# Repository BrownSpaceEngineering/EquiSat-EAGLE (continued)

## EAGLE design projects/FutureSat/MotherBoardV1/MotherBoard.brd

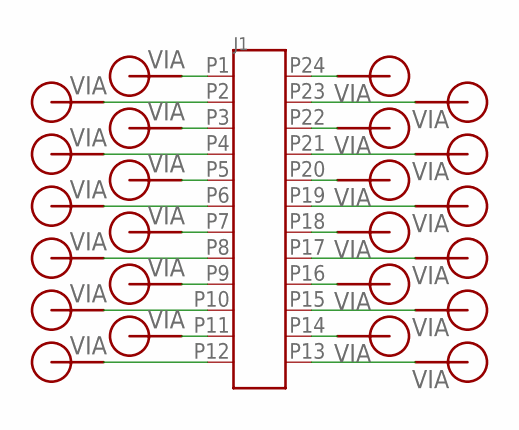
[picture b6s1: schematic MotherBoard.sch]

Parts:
J1: EBM12DRXH
V1, V2, V3, V4, V5, V6, V7, V8, V9, V10, V11, V12, V13, V14, V15, V16, V17, V18, V19, V20, V21, V22, V23, V24: VIA60MIL-SQ; VIA-60MIL-SQ

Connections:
unnamed: J1.P1, V1.P$1
unnamed: J1.P2, V2.P$1
unnamed: J1.P3, V3.P$1
unnamed: J1.P4, V4.P$1
unnamed: J1.P5, V5.P$1
unnamed: J1.P6, V6.P$1
unnamed: J1.P7, V7.P$1
unnamed: J1.P8, V8.P$1
unnamed: J1.P9, V9.P$1
unnamed: J1.P10, V10.P$1
unnamed: J1.P11, V11.P$1
unnamed: J1.P12, V12.P$1
unnamed: J1.P13, V13.P$1
unnamed: J1.P14, V14.P$1
unnamed: J1.P15, V15.P$1
unnamed: J1.P16, V16.P$1
unnamed: J1.P17, V17.P$1
unnamed: J1.P18, V18.P$1
unnamed: J1.P19, V19.P$1
unnamed: J1.P20, V20.P$1
unnamed: J1.P21, V21.P$1
unnamed: J1.P22, V22.P$1
unnamed: J1.P23, V23.P$1
unnamed: J1.P24, V24.P$1

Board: 2 copper layers, 25 parts (0 on the bottom side), 24 nets, no tracks yet.

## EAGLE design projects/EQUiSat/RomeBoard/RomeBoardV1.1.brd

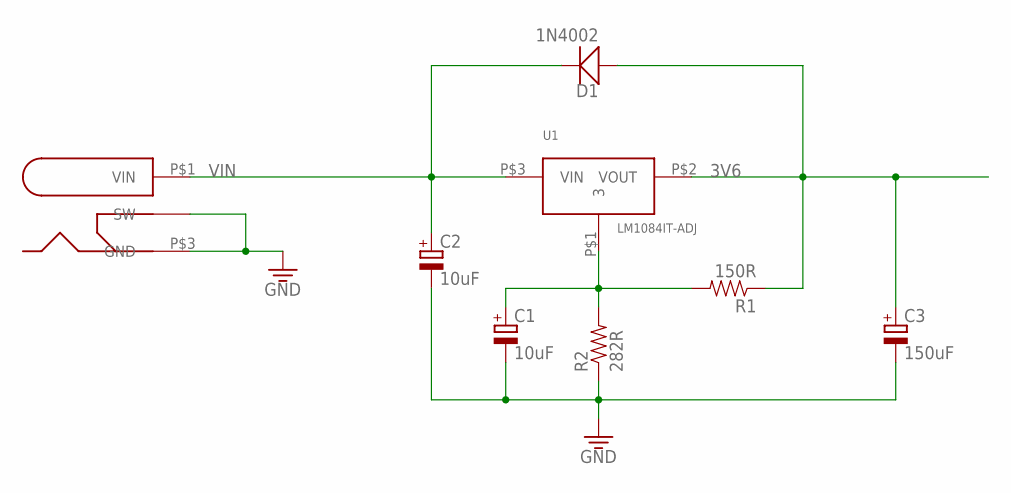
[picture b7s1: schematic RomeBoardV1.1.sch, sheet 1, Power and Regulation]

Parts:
C1, C2: 10uF; E2,5-7
C3: 150uF; E5-13
D1: 1N4002; DO-201AD
R1: 150R; AXIAL-0.4
R2: 282R; AXIAL-0.4
U1: LM1084IT-ADJ; TO-220-507302B00000G
U$2: PJ-002A

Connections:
3V6: C3.+, D1.P$1 (A), R1.1, U1.P$2 (VOUT); also elsewhere on the board
GND: C1.-, C2.-, C3.-, R2.1, U$2.P$2 (SW), U$2.P$3 (GND); also elsewhere on the board
unnamed: C1.+, R1.2, R2.2, U1.P$1 (3)
VIN: C2.+, D1.P$2 (C), U1.P$3 (VIN), U$2.P$1 (VIN); also elsewhere on the board

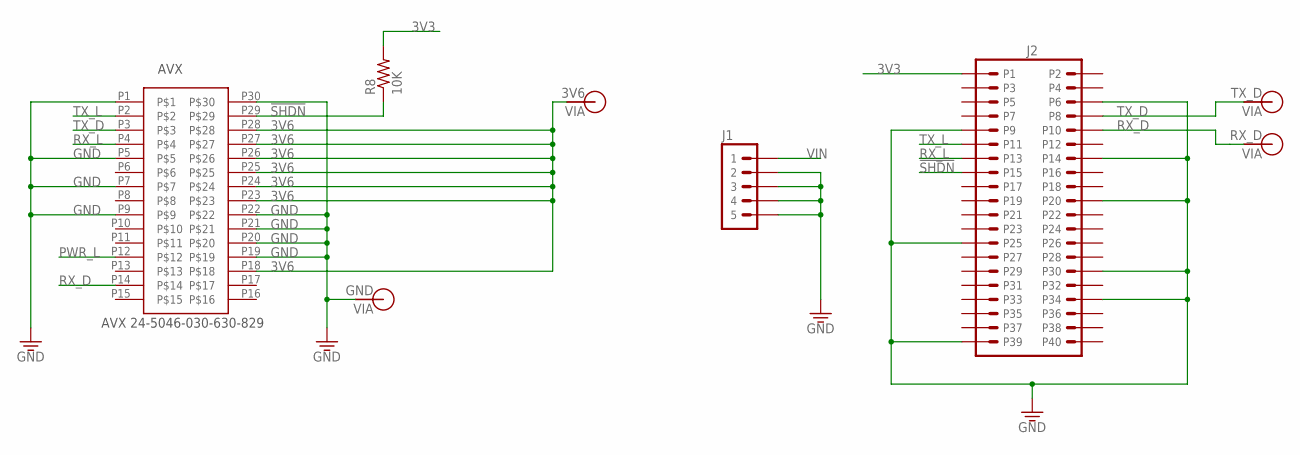
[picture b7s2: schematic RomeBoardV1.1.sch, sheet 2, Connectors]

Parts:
AVX: AVX-24-5046-030-630-829; AVX-24-5046-630-829
J1: HEADER-5; HEADER-05
J2: RASPBERRY-PI-HEADER; HEADER-20X02
R8: 10K; AXIAL-0.4
V1: TX_D; VIA-120MIL
V2: RX_D; VIA-120MIL
V4: GND; VIA-120MIL
V5: 3V6; VIA-120MIL

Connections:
3V3: J2.P1, R8.2
3V6: AVX.P18, AVX.P23, AVX.P24, AVX.P25, AVX.P26, AVX.P27, AVX.P28, V5.P$1; also elsewhere on the board
!SHDN: AVX.P29, J2.P15, R8.1
GND: AVX.P1, AVX.P5, AVX.P7, AVX.P9, AVX.P19, AVX.P20, AVX.P21, AVX.P22, AVX.P30, J1.2, J1.3, J1.4, J1.5, J2.P6, J2.P9, J2.P14, J2.P20, J2.P25, J2.P30, J2.P34, J2.P39, V4.P$1; also elsewhere on the board
PWR_L: AVX.P12; also elsewhere on the board
RX_D: AVX.P14, J2.P10, V2.P$1
RX_L: AVX.P4, J2.P13; also elsewhere on the board
TX_D: AVX.P3, J2.P8, V1.P$1
TX_L: AVX.P2, J2.P11; also elsewhere on the board
VIN: J1.1; also elsewhere on the board

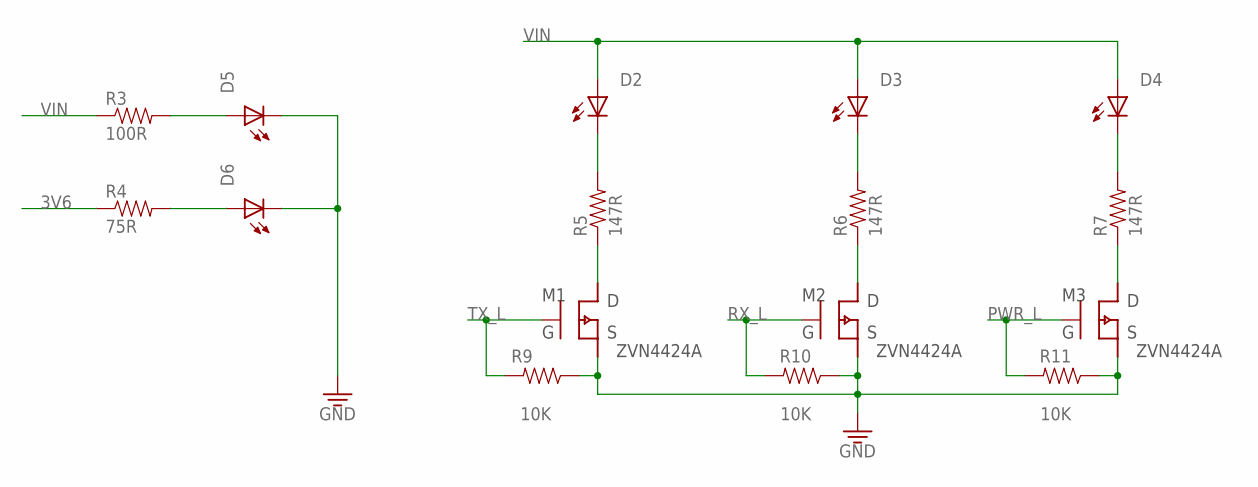
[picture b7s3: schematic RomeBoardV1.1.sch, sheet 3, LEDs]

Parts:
D2, D3, D4, D5, D6: LEDTHRU-HOLE-CONNECTOR; 1X2-POL
M1, M2, M3: ZVN4424A; TO-923-MOS
R3: 100R; AXIAL-0.4
R4: 75R; AXIAL-0.4
R5, R6, R7: 147R; AXIAL-0.4
R9, R10, R11: 10K; AXIAL-0.4

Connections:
3V6: R4.1; also elsewhere on the board
GND: D5.2 (C), D6.2 (C), M1.3 (S), M2.3 (S), M3.3 (S), R9.1, R10.1, R11.1; also elsewhere on the board
unnamed: D5.1 (A), R3.2
unnamed: D6.1 (A), R4.2
unnamed: D3.2 (C), R6.2
unnamed: M1.1 (D), R5.1
unnamed: M2.1 (D), R6.1
unnamed: M3.1 (D), R7.1
unnamed: D4.2 (C), R7.2
unnamed: D2.2 (C), R5.2
PWR_L: M3.2 (G), R11.2; also elsewhere on the board
RX_L: M2.2 (G), R10.2; also elsewhere on the board
TX_L: M1.2 (G), R9.2; also elsewhere on the board
VIN: D2.1 (A), D3.1 (A), D4.1 (A), R3.1; also elsewhere on the board

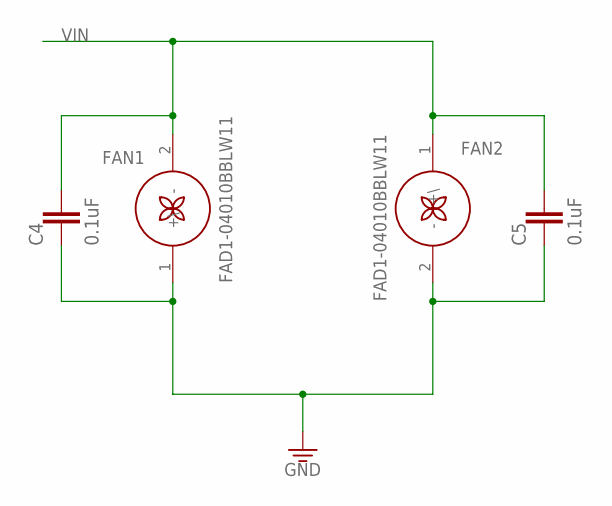
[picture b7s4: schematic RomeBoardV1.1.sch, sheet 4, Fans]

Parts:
C4, C5: 0.1uF; C050-025X075
FAN1, FAN2: FAD1-04010BBLW11; 1X2-POL

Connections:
GND: C4.2, C5.2, FAN1.1 (+\), FAN2.2 (-); also elsewhere on the board
VIN: C4.1, C5.1, FAN1.2 (-), FAN2.1 (+\); also elsewhere on the board

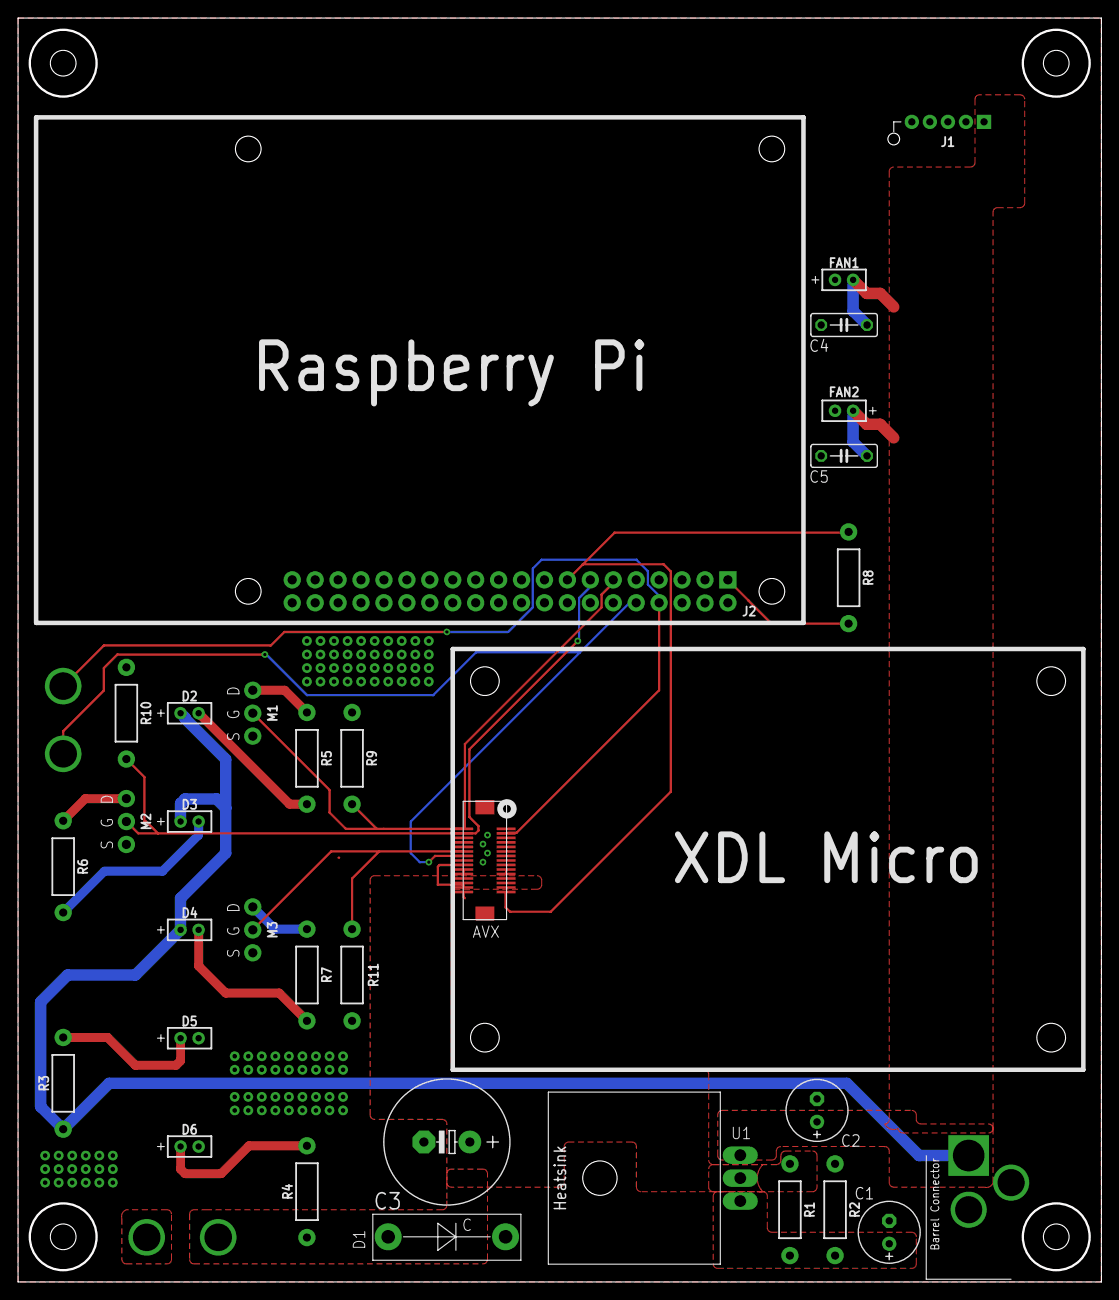
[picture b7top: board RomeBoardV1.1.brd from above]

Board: 2 copper layers, 120.0 x 140.0 mm, 36 parts (0 on the bottom side), 19 nets.

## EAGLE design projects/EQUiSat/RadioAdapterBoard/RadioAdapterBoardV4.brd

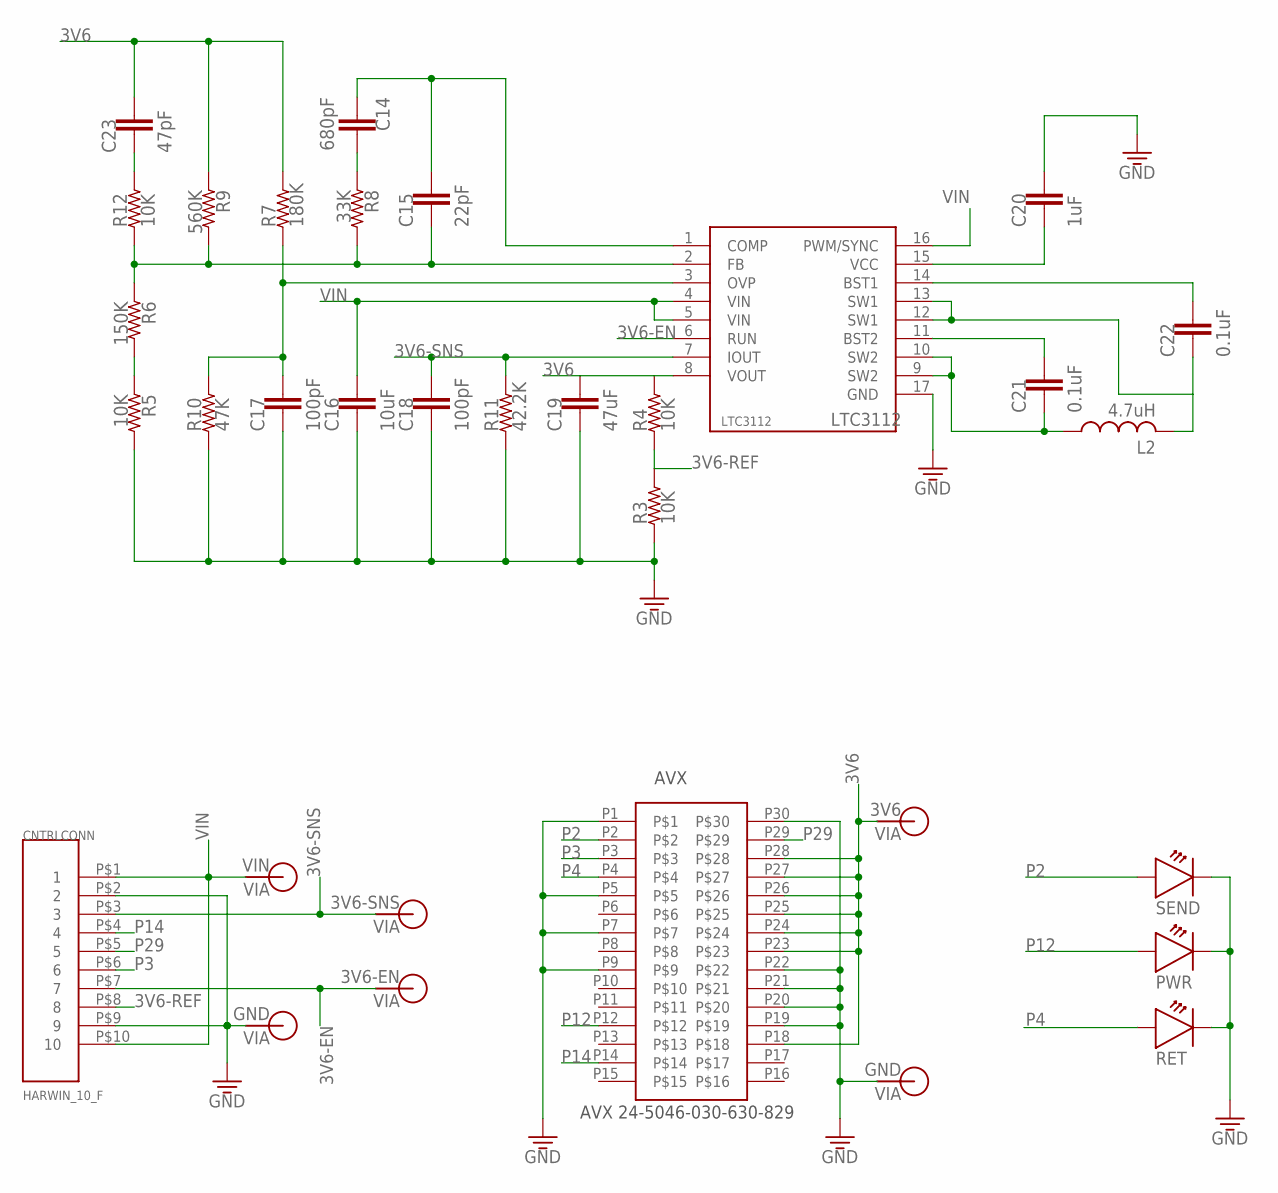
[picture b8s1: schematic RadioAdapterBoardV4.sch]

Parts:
AVX: AVX-24-5046-030-630-829; AVX-24-5046-630-829
C14: 680pF; 0805
C15: 22pF; 0805
C16: 10uF; 0805
C17, C18: 100pF; 0805
C19: 47uF; 0805
C20: 1uF; 0805
C21, C22: 0.1uF; 0805
C23: 47pF; 0805
CNTRLCONN: HARWIN_10_F; HARWIN_DATAMATE_10_F
L2: 4.7uH; L3225M
LTC3112: LTC3112; DHD16
PWR: LT-T673-Q1R2-25-Z; PLCC-2
R3, R4, R5, R12: 10K; 0805
R6: 150K; 0805
R7: 180K; 0805
R8: 33K; 0805
R9: 560K; 0805
R10: 47K; 0805
R11: 42.2K; 0805
RET: LT-T673-Q1R2-25-Z; PLCC-2
SEND: LT-T673-Q1R2-25-Z; PLCC-2
V1: VIN; VIA-60MIL-SQ
V2: 3V6-SNS; VIA-60MIL-SQ
V3, V4: GND; VIA-60MIL-SQ
V5: 3V6; VIA-60MIL-SQ
V6: 3V6-EN; VIA-60MIL-SQ

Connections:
3V6: AVX.P18, AVX.P23, AVX.P24, AVX.P25, AVX.P26, AVX.P27, AVX.P28, C19.1, C23.1, LTC3112.8 (VOUT), R4.2, R7.2, R9.1, V5.P$1
3V6-EN: CNTRLCONN.P$7 (7), LTC3112.6 (RUN), V6.P$1
3V6-REF: CNTRLCONN.P$8 (8), R3.2, R4.1
3V6-SNS: C18.1, CNTRLCONN.P$3 (3), LTC3112.7 (IOUT), R11.2, V2.P$1
COMP: C14.2, C15.1, LTC3112.1 (COMP)
FB: C15.2, LTC3112.2 (FB), R6.1, R8.2, R9.2, R12.1
GND: AVX.P1, AVX.P5, AVX.P7, AVX.P9, AVX.P19, AVX.P20, AVX.P21, AVX.P22, AVX.P30, C16.2, C17.2, C18.2, C19.2, C20.1, CNTRLCONN.P$2 (2), CNTRLCONN.P$9 (9), LTC3112.17 (GND), PWR.C, R3.1, R5.2, R10.1, R11.1, RET.C, SEND.C, V3.P$1, V4.P$1
unnamed: C22.2, L2.2, LTC3112.12 (SW1), LTC3112.13 (SW1)
unnamed: C14.1, R8.1
unnamed: C23.2, R12.2
unnamed: R5.1, R6.2
unnamed: C20.2, LTC3112.15 (VCC)
unnamed: C22.1, LTC3112.14 (BST1)
unnamed: C21.2, L2.1, LTC3112.9 (SW2), LTC3112.10 (SW2)
unnamed: C21.1, LTC3112.11 (BST2)
OVP: C17.1, LTC3112.3 (OVP), R7.1, R10.2
P2: AVX.P2, SEND.A
P3: AVX.P3, CNTRLCONN.P$6 (6)
P4: AVX.P4, RET.A
P12: AVX.P12, PWR.A
P14: AVX.P14, CNTRLCONN.P$4 (4)
P29: AVX.P29, CNTRLCONN.P$5 (5)
VIN: C16.1, CNTRLCONN.P$1 (1), CNTRLCONN.P$10 (10), LTC3112.4 (VIN), LTC3112.5 (VIN), LTC3112.16 (PWM/SYNC), V1.P$1

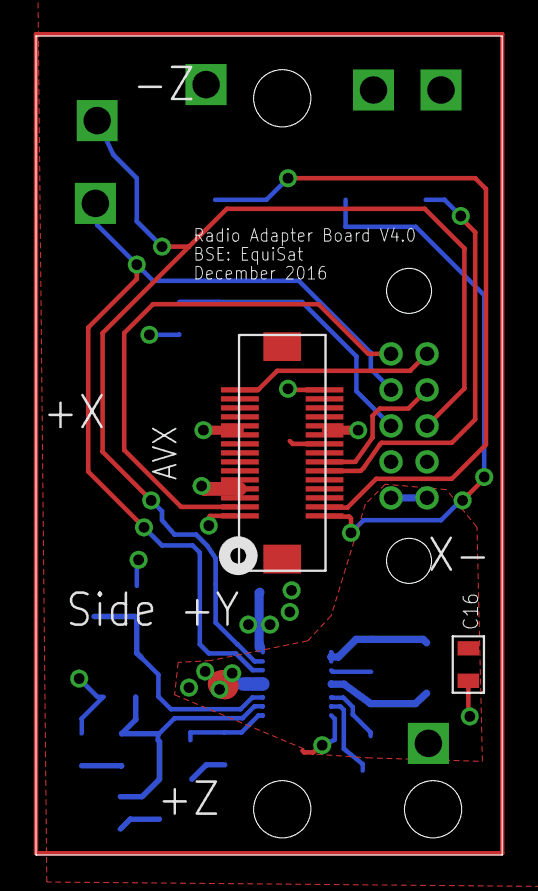
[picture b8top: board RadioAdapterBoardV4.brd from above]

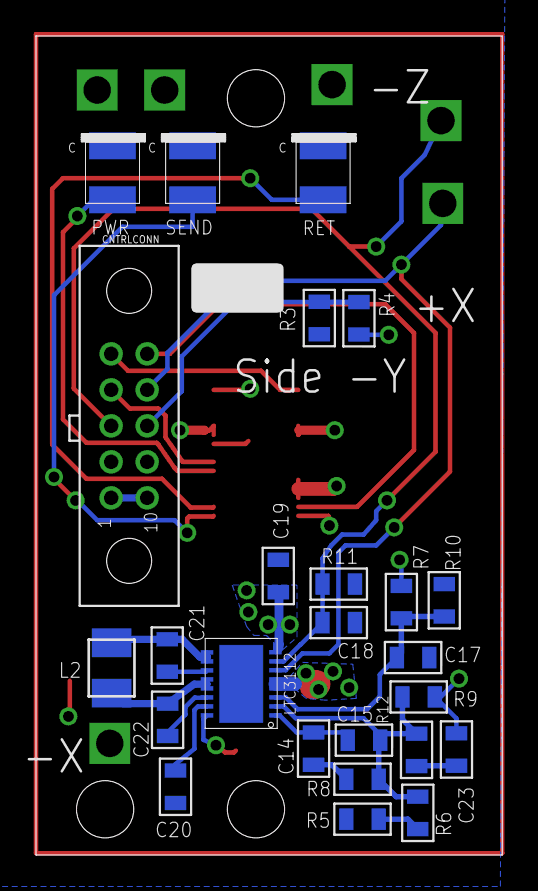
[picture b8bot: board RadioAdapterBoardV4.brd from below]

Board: 2 copper layers, 25.9 x 45.5 mm, 33 parts (25 on the bottom side), 23 nets.

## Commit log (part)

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2016-07-10 Initial commit of existing EquiSat EAGLE files
2016-08-29 Added Side Panel V4
2016-09-02 fixed side panel
2016-09-03 Added top panel v4
2016-09-03 Touched up top and side panels
2016-09-04 Updated access panel
2016-09-04 fixed
2016-09-08 Top and Side Panels, Proc Test Board prepared for production
2016-09-22 I don't know
2016-10-16 added new library
2016-10-27 Added 3V6-SNS, 3V6-EN, 3V6-REF to Radio Adapter Board
2016-10-27 Changes to Radio Adapter Board V4
    Moved LEDs to Radio Adapter Board
    Flipped the connection to the radio so the radio is pointing into the
    board
2016-10-30 changes to Radio Adapter Board V4
    Added the connections to LTC3112
2016-10-30 Changes to Radio Adapter Board
    In Process of Optimizing the Physical Layout
2016-11-03 Radio Adaptor Board Minor Updates
2016-11-05 Battery Board Li-Ion charging circuit finished.
2016-11-05 Li-ion batteries added to battery charging
2016-11-06 Continued work on LiFePO4 charging and library updates
2016-11-06 Updates to the Radio Adapter Board
2016-11-13 small edit
2016-11-13 Radio Control Board Preliminary Wiring Completed
2016-11-13 Fixed Radio Adaptor Board
2016-11-17 Radio Adapter Board Design in Progress
    Still working on routing
2016-11-17 added usb 24 pin connector part
2016-11-20 Small updates to Flash Panel V6.2
2016-11-20 Radio Adapter Board Layout Almost Done
2016-11-20 Started updating Driver Board, made V1.2
2016-11-22 Cleaned up Git tracked files. Changes/additions to libraries. Addition of missing LED library part. Began Battery Board layout.
2016-11-27 Nearly finished placement of battery board, continued library updates and touch ups on all active boards/schematics.
2016-11-28 Finished Battery Board layout and first draft of routing. Ready for final review. Additional library updates.
2016-11-28 Finished second round of Battery Board Layout
2016-11-29 Small fixes to Battery Board Layout
2016-11-30 Finalized Battery Board - board has been ordered.
2016-12-01 Updates to driverboard and driverboard library
2016-12-01 Small updates to driverboard lib
2016-12-04 Worked on updating Driver Board,e V1.2
2016-12-04 began updating flash panel V6.2
2016-12-04 Added connector to driverboard lib
2016-12-08 Revert to 34566699e3a693507405c41ff6389c8b0b8f54b4
2016-12-08 Revert to 38f23719aba36e713c9775b9fa583fd5065d9ba1
2016-12-08 added archive files
2016-12-08 Deleted more problematic files
2016-12-11 Finished RAB Layout . . . again
    Needs to be checked by Ryan!!
    Labels might need to be moved around.
2016-12-12 Radio Adapter Board PCB Ready
    Also, minor edits to 0805 package, L3255M package, and job
    sfe-ger274x.cam
2016-12-20 Initial Commit of Equisat Simulator
2017-01-12 Completion of AccessPanelV3 and updates to libraries. Renamed SidePanelV4 to match standard.
2017-01-12 Actual commit with library changes and renaming
2017-01-29 Bill of Materials text for Access Panel V3
2017-01-29 Removed txt document and some continued Flash and Driver board updates.
2017-02-09 Completed all changes to Flash Panel and Driver Board. Additional library changes and additions for antenna deployment detection circuitry.
2017-02-09 Initial commit of Control Board V3 and library updates to support that.
2017-02-13 Finalized Flash Panel and Driver Board
2017-02-14 Added in the pcb borders to flash panel and driver board for fab.
2017-02-21 Continued Control Board Updates and library updates. Added Multiplexers, Opamps, Diodes, multiplexing circuitry, instrumentation circuitry, and remote ADC.
2017-02-21 Added photodiode instrumentation circuit
2017-02-26 Completed first round of cntrl board placement for all components.
2017-02-27 Continued work on Control Board layout - modification of some connector types and connector pinouts to optimize routing, initial power and ground routing.
2017-02-27 Completed first round of Control Board routing and silkscreen marker placement. Gonna sleep on it and see how I like it in the morning.
2017-02-27 Added test vias and LEDs for testing and monitoring. Cleaned up asthetics and added documentation on silkscreen
2017-02-28 Fixed problem with processor pin mapping, rerouted accordingly. Final adjustments for production. Ready to order.
2017-02-28 Forgot to give values to 3 resistors. Doesn't impact board at all - just BOM
2017-04-09 Side Panel V5
2017-05-12 V1
    fixed a wire
2017-07-07 Programmer Board V1.1
2017-07-23 moved connector + rearranged vias
    USB connector now as close to edge as possible, vias arranged so
    grounds are more spread out and board is more compact
2017-07-25 added protection circuit AP9211
2017-07-26 adding AD8418 current sense amp
2017-07-26 Adding more circuitry
    Fixed Li-ion protection circuit
    Added option of pullup (0R) resistor to INVCC for FREQ pins, and added
    option of pulldown (10K) resistor to ground for FREQ
    Added current sense circuitry to Li-ion and Lifepo bank
2017-07-27 Added finishing circuitry
    Added PTC fuses
    Added vias for all charging inputs and outputs
2017-07-29 Adding zener diode BZX84C7V5LT1G and fixing part names
2017-07-29 Different zener diode to meet current reqs
2017-07-29 adding zener diode SMBJ5343B-TP
2017-07-30 side panel v5 WIP
    updated cells
    still figuring out cell layout
2017-07-31 Side Panel V5 Finished (?)
    Ready to be checked
2017-08-03 Side Panel V5 In Review (Part III)
    > Added diode and 0R resistor in parallel between the cells' output and
    PWR-OUT (this circuit is being moved from Battery Board V1).
    > Top layer is now the CELL-OUT signal.
    > Put C1 on bottom layer.
    > Moved all the vias further away from the cells.
    > Connected the corner screw holes to GND.
2017-08-03 LifePo separated out
    this is by no means anywhere near complete - i just put the lifepo
    stuff on one side and gave it a basic layout. any feedback is welcome
    though
2017-08-04 Fixed ERC issues
    ERC still complains about some power connections but I think these are
    fine
2017-08-04 Side Panel V5 Finished
    > Added +Z and -Z direction labels.
2017-08-06 Added LC05111C13MTTTG as an alternate to AP9211SA-AG-HAC-7
    I am still a little skeptical on the AP9211SA-AG-HAC-7’s discharge
    current limit. LC05111C13MTTTG explicitly defines it as 3A, which is a
    lot more reassuring than what the AP9211SA-AG-HAC-7 has to say about it.
    For AP9211SA-AG-HAC-7, maximum discharge current was found by
    V_overdischargelimit / R_SS(on). Gives an answer that works out with
    power limit, but it’s still weird that the maximum discharge is not
2017-08-06 Lifepo layout improved a bit (nothing major this time)
2017-08-06 Top Panel V5 WIP
    > Copied from Access Panel V3.
    > Deleted the umbilical connector and associated vias.
    > NEEDS FINALIZED DIMENSIONS BEFORE MORE WORK CAN BE DONE
2017-08-08 about to play with the autorouter
2017-08-08 hand-routed high current paths
2017-08-08 Autorouted board (with islands to be fixed)
2017-08-09 Manually routed most of board
2017-08-09 Routed board
2017-08-09 Silkscreen information
2017-08-13 More comments incorp.
2017-08-14 Completed TopPanelV5 with new board dimensions and cells. Ready for rewview/fab
2017-08-14 Modified Top Panel V5 layout to optimize for wiring.
2017-08-14 Additional edits to Access Panel V4 layout. Just needs the access connector.
2017-08-15 Added new access panel connector and completed AccessPanelV4.
2017-08-15 Initial commit of ABFPanelV1 and cosmetic changes to SidePanelV5 (change square vias to circular).
2017-08-16 Giving layout another shot (Li-ion done)
2017-08-16 Swapping pads on battery chargers per Trello card
2017-08-18 This now definitely fixes both LTC4142 and LTC4142-4.2
2017-08-18 Board ready for Ryan review
2017-08-19 included Ryan feedback
2017-08-19 Fixing LC05111 pinout
2017-08-23 Better current sense routing
2017-08-24 Created PracticeBoardV1; removed .l# files cluttering the lib_dr folder
    > Added 3V3 regulator from ControlBoardV3 to schematic of PracticeBoardV1
2017-08-24 Added the SN74LV04A-Hex-Inverter and corresponding package 14-TSSOP to BSE lib
    > Also worked on prepping the PracticeBoardV1 board a tiny bit
2017-08-25 Silkscreen text vectorized
2017-08-25 Added AND, NAND, OR, XOR and OP Amp to BSE Lib
    > For use with the PracticeBoard
2017-08-25 Fixing some ERC
2017-08-26 Added coin battery holder to lib; Added astable timer and AND/OR led circuit to PracticeBoardV1
    Still need the LED enable circuit from ControlBoard ???
2017-08-28 PracticeBoardV1 Schematic Review II
    > Added thru-hole diode and potentiometer to library
    > Added via "switch" to the battery
    > Added a second battery in series (each one has end-to-end voltage of
    ~2V)
    > Removed unnecessary components
    > Fixed (?) astable timing circuit
2017-08-29 Added RBF switches to library. (changed ABF to RBF) Added RBF switches and routing to RBF Panel. Vectorized all text on solar panel boards and rearranged as needed.
2017-08-30 Adjusted board layout for sizing. Added notes to silkscreen for ease of operation. Removed bottom silkscreen. Added 10k pull-down resistors to logic inputs.
2017-08-30 Added keepout zones on battery part package. Update libraries in parts to implement.
2017-08-30 PracticeBoardV1--renumbered parts
2017-08-31 Touch ups to Practice Board to fix DFM problems. Changed the TPS63001 package to get rid of DFM errors.
2017-08-31 Adding all of the latest gerbers. Going to expand on this, but this is a first step to having a back-ed up version on github of every board and it's manufacturing files exactly as ordered.
2017-09-01 Fixed bottom silkscreen of RBFPanelV1 that refered to it as ABF Panel. Added Gerber .zip files to directories. All Solar Panels and Practice board are ready for order
2017-09-04 Initial commit of Battery Board V2. Removed almost all V1 layout, changed lion chargers to -4.2 PN but not updated circuitry. Rotated lion batteries. Removed superfluous vias. Started LDO circuit all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
2017-09-05 Finished programmer board and added output files to repo. Addiong of LDOs and continued fixes and updates to battery board v2.
2017-09-10 Continued improvements to the Battery Board schematic. Board reshaped.
2017-09-10 Cleaning up .s#1, .b#1, and .lck files.
2017-09-20 Fixed the VQFN-14 Package (pins were reversed)
    Note, the AND circuit of the PracticeBoardV1 will not function
2017-09-24 Addition of zener diodes. Updates to some resistor values. Inital layout of all Li-ion circuitry.
2017-09-25 Finished inital placement of all components on the battery board. Updated pull-down values for high-side switch input resistor.
2017-09-29 Finished Battery Board V2. Verified all nets connected, silkscreens are readable, axes identified, no overlapping polygons. Created Gerber files, Gerber zip, and schematic pdf.
2017-09-30 Fixing board outline problem for manufacturability.
2017-12-19 Updating schematic for battery board, adding schematic for flight configuration
2017-12-20 putting in correct directory
2017-12-22 take 5 - trying to fix this directory
2018-01-27 Initial Commit of Battery Board V3. Made all changes in schematic and removed invalid polygon pours on board.
2018-01-28 Adding soldering footprint for LiFePo current sense resistor
2018-01-28 Completed layout
2018-01-29 move R64 silkscreen
2018-01-29 one GPIO pin wasn't connected
2018-04-09 +LM2576 regulator
2018-04-09 Package fixes, small updates to schematic
2018-04-11 Adding more parts + moving layout around
2018-04-11 Reorganizing regulator
2018-04-13 NPN -> NMOS
2018-04-17 Board layed out but unrouted
2018-04-23 Board + Schematic routed
2018-04-24 Improved routing, added silkscreen infos
2018-04-25 Small improvements
2018-04-27 V1.1 initial commit
2018-04-27 fixing air wire + updating library
2018-04-30 Adding fan connectors to board, increasing board size, re-routing some stuff
2018-04-30 Adding gate pulldowns for NPNs
2018-04-30 Adding rev B board
    Major change - Pi no longer soldered to board, but instead a ribbon
    cable is used to connect the Pi to the board.
2018-05-02 final version of 1.1B (pending very minor changes)
2018-05-04 small change
2018-07-16 Adding RomeBoard v1.2
2018-07-19 Silkscreen tweaks
2018-09-04 Renaming directories
    renamed the BSE EAGLE directories to match the names of the default EAGLE directories
    makes it easier to set up EAGLE
2019-03-11 Revert "test commit"
    This reverts commit 30def762e65aeb92ff89bbefb99a29b593c2f5d6.
2019-03-11 Added edge connector to new FutureSat library; added MotherBoardV1 (WIP); reorgainzed all folders to separate EQUiSat and FutureSat
